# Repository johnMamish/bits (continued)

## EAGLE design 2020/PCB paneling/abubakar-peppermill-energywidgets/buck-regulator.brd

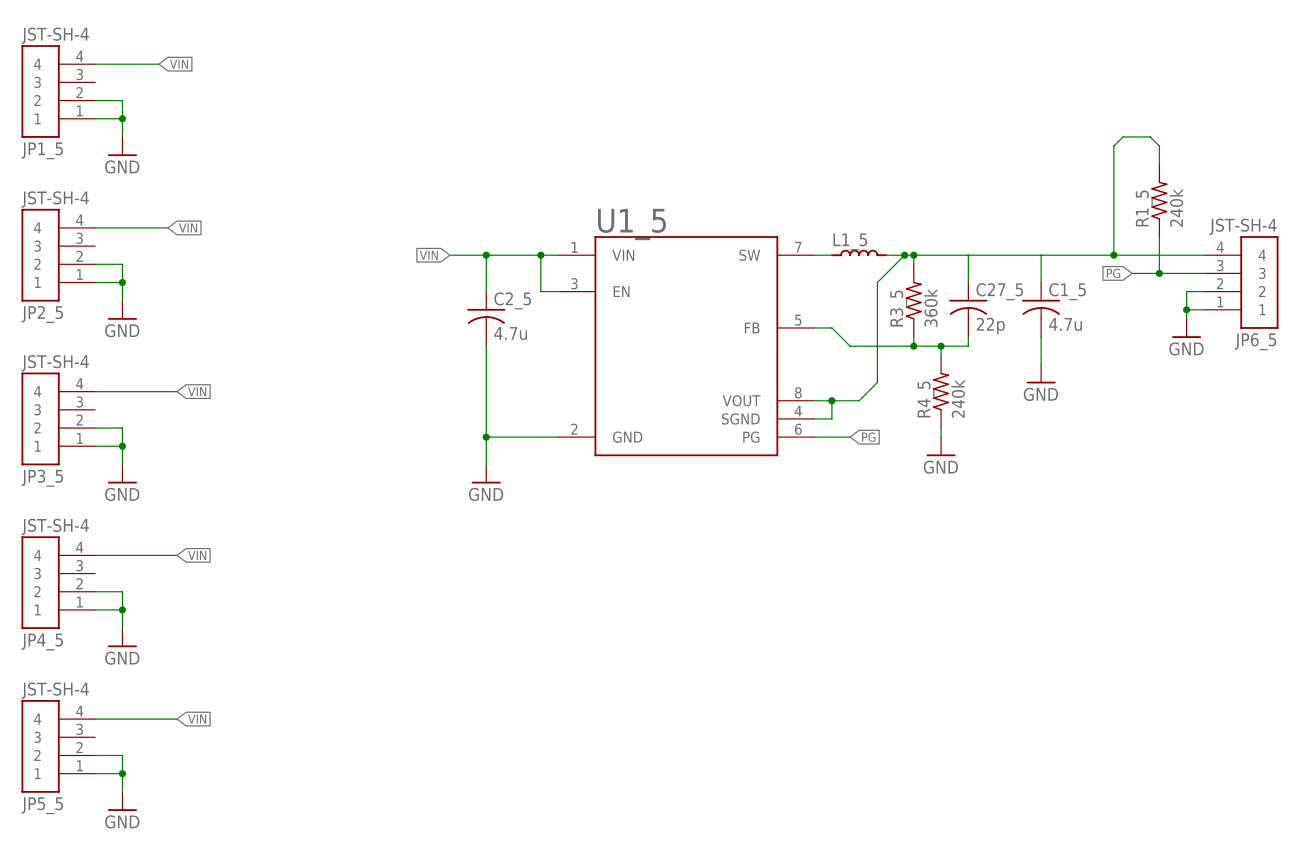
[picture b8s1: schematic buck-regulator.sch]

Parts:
C1_5, C2_5: 4.7u; C0603; MFR_PN CL10A475KA8NQNC
C27_5: 22p; C0402; MFR_PN C0603C220J5GACTU
JP1_5, JP2_5, JP3_5, JP4_5, JP5_5, JP6_5: JST-SH-4; MFR_PN SM04B-SRSS-TB(LF)(SN)
L1_5: 22u; LQH3NPNXXXXMEX; MFR_PN LQH3NPN220MJRL
R1_5, R4_5: 240k; R0603; MFR_PN ERJ-3GEYJ244V
R3_5: 360k; R0603; MFR_PN ERJ-3GEYJ364V
U1_5: TPS62120; SOP65P280X145-8N; MFR_PN TPS62120

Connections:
BUCK_OUT: C1_5.1, C27_5.1, JP6_5.4, L1_5.P$2, R1_5.2, R3_5.2, U1_5.4 (SGND), U1_5.8 (VOUT)
GND: C1_5.2, C2_5.2, JP1_5.1, JP1_5.2, JP2_5.1, JP2_5.2, JP3_5.1, JP3_5.2, JP4_5.1, JP4_5.2, JP5_5.1, JP5_5.2, JP6_5.1, JP6_5.2, R4_5.1, U1_5.2 (GND)
unnamed: C27_5.2, R3_5.1, R4_5.2, U1_5.5 (FB)
unnamed: L1_5.P$1, U1_5.7 (SW)
PG: JP6_5.3, R1_5.1, U1_5.6 (PG)
VIN: C2_5.1, JP1_5.4, JP2_5.4, JP3_5.4, JP4_5.4, JP5_5.4, U1_5.1 (VIN), U1_5.3 (EN)

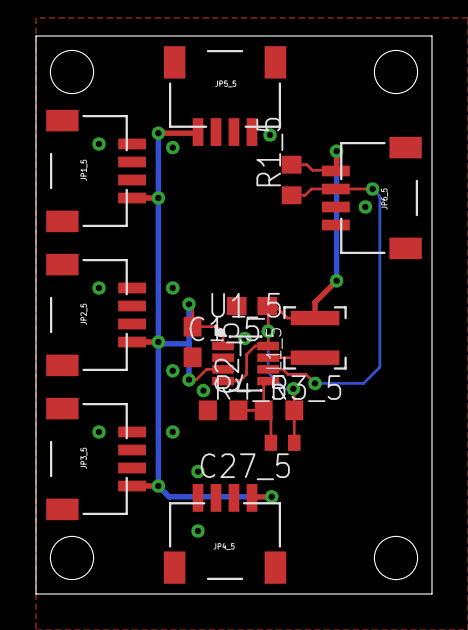
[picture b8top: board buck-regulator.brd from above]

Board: 2 copper layers, 22.0 x 31.0 mm, 14 parts (0 on the bottom side), 6 nets.

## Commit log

2017-06-17 worked on usb and box of cute
2017-06-17 work on box of cute
2017-06-17 work on cutebox
2017-06-18 first version works
2017-06-18 first fully working version
2017-06-20 memory leaks fixed on serial usb matchup
2017-06-20 usb serial mapper passes smoke test
2017-10-02 not sure what this stuff was
2017-10-02 matfun multiply passes smoke test
2017-10-02 characteristic polynomial calculation passes smoke test
2020-08-05 add new files from 2020
2020-08-06 add Eagle BOM and pick and place merging python script for pcb ng
2020-08-09 quartus, nes controller beep
2020-08-09 add wm8731 and NES controller readme
2020-08-10 add more quartus
2020-08-13 stuff
2020-08-22 grayscale sampler verilog
2020-08-22 grayscale downsampler wip
2020-08-23 grayscale downsampler passes basic testbench
2020-12-01 update pcbng merge script a bit
2020-12-29 add a bunch of stuff
2021-01-27 ergcalc
2021-02-01 notes on microchip samd fuses
2025-01-31 ecp5 bringup
2025-02-05 add ecp5 lattice blinky
2025-02-06 ecp5 camera
2025-02-06 i2c stuff ecp5
2025-02-13 hm0360 on ecp5 wip
2025-02-13 initializer program wip
2025-02-13 initializer program works
2025-02-14 dual camera read wip
2025-03-25 ft232h async writer passes smoke test
2025-03-26 ft232h reader passes smoke test
2025-03-30 reading images with the ft232 passes smoke test
2025-03-30 ft232h gui working pretty well
2025-05-01 add some features to serialcam
2025-05-02 add some updates to ft232
